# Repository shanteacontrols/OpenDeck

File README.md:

# OpenDeck

OpenDeck is a platform for building interactive control and sensing devices using MIDI and OSC. From USB MIDI DJ controllers and DAW control surfaces to Ethernet-connected OSC nodes, sensor interfaces and media installations, OpenDeck supports a wide range of hardware projects.

The main platform features:

* Browser-based configuration
* No firmware development required
* Hardware-independent - supports multiple MCU families and development boards
* MIDI and OSC support
* Extensible sensor support

The platform lets you focus on hardware and interaction design rather than tweaking and debugging firmware.

*Click the image below for a demo video of the [OpenDeck configurator](https://config.shanteacontrols.com)*

Configurator is available either [online](https://config.shanteacontrols.com) or [offline](https://github.com/shanteacontrols/OpenDeckUI/releases).

*Some of the devices built with OpenDeck*

## Peripherals

OpenDeck supports the following peripherals:

### Core I/O

* Buttons
* Encoders
* Single-color LEDs and other types of outputs such as relays or transistors
* Potentiometers
* FSRs (force-sensitive resistors)

### Displays

* [Nextion HMI](https://nextion.tech/) touchscreen displays
* [SSD1306 small OLED display](https://www.adafruit.com/product/326)

### Sensors

* [APDS-9960 proximity, light, RGB, and gesture sensor](https://www.adafruit.com/product/3595) - OSC only
* [CAP1188 8-Key Capacitive Touch Sensor](https://www.adafruit.com/product/1602) - OSC only
* [VL53L4CX time of flight distance sensor](https://www.adafruit.com/product/5425) - OSC only
* [VL53L5CX 8x8 time of flight distance sensor](https://www.sparkfun.com/sparkfun-qwiic-tof-imager-vl53l5cx.html) - OSC only
* [BNO085 9-DOF orientation IMU fusion sensor](https://www.adafruit.com/product/4754) - OSC only

Each sensor has specific configuration options such as smoothing, selectable event output etc.

## Features

OpenDeck provides extensive MIDI and OSC functionality:

* MIDI: sending of both 7-bit and 14-bit Non-Registered Parameter Numbers (NRPN), latching messages on buttons, various encoding modes for quadrature encoders, output control using MIDI In, configurable MIDI channels for each component individually, Bluetooth MIDI and more.
* OSC: Ethernet transport, configurable destinations, sensor data streaming, output control, automatic network discovery via mDNS, network-based configuration and firmware updates.

A detailed guide to all supported configurable features can be found [here](https://github.com/shanteacontrols/OpenDeck/wiki/Configurable-features).

If the feature you want isn't supported yet, don't feel discouraged. Open up a [discussion thread](https://github.com/shanteacontrols/OpenDeck/discussions) and let's talk about it.

## Official board

Currently, there is only one official board available to buy: the L variant, where "L" stands for "large". The board is available on [Lectronz store](https://lectronz.com/products/opendeck-l/).

This board is based on Raspberry Pi RP2040 microcontroller and features the following:

* 128 digital inputs
* 64 digital outputs
* 64 analog inputs
* DIN MIDI
* USB MIDI (USB C)
* Connector for touchscreen
* Connector for I2C OLED display
* Additional connectors with 3V+GND and 5V+GND connections

The L board doesn't have OSC support. It focuses on providing lots of I/O specifically for USB and DIN MIDI use-cases. OSC functionality is available on a number of supported Ethernet-enabled boards.

## Supported boards

The firmware supports various other boards, both small and large:

| Board | MIDI | OSC |
| --- | --- | --- |
| [Adafruit Grand Central M4 Express](https://www.adafruit.com/product/4064) | USB, DIN | No |
| [Adafruit Metro ESP32-S3](https://www.adafruit.com/product/5500) | USB, DIN | No |
| [Adafruit Metro ESP32-S3](https://www.adafruit.com/product/5500) + [W5500 Ethernet Shield](https://wiznet.io/products/open-source-hardware/w5500-ethernet-shield) | USB | Ethernet |
| [Adafruit Metro ESP32-S3](https://www.adafruit.com/product/5500) + [W6100 Ethernet Shield](https://wiznet.io/products/open-source-hardware/w6100-ethernet-shield) | USB | Ethernet |
| [Adafruit Metro RP2040](https://www.adafruit.com/product/5786) | USB, DIN | No |
| [Adafruit Metro RP2040](https://www.adafruit.com/product/5786) + [W5500 Ethernet Shield](https://wiznet.io/products/open-source-hardware/w5500-ethernet-shield) | USB | Ethernet |
| [Adafruit Metro RP2040](https://www.adafruit.com/product/5786) + [W6100 Ethernet Shield](https://wiznet.io/products/open-source-hardware/w6100-ethernet-shield) | USB | Ethernet |
| [Arduino Nano 33 BLE](https://store.arduino.cc/products/arduino-nano-33-ble) | USB, DIN, BLE | No |
| [LILYGO T-ETH Elite](https://lilygo.cc/products/t-eth-elite-1) | USB | Ethernet |
| [nRF52840 DK](https://www.nordicsemi.com/Products/Development-hardware/nrf52840-dk) | USB, DIN, BLE | No |
| [nRF5340 DK](https://www.nordicsemi.com/Products/Development-hardware/nrf5340-dk) | USB, DIN, BLE | No |
| [Olimex ESP32-POE](https://www.olimex.com/Products/IoT/ESP32/ESP32-POE/open-source-hardware) | No | Ethernet |
| [Raspberry Pi Pico](https://www.raspberrypi.com/products/raspberry-pi-pico/) | USB, DIN | No |
| [Raspberry Pi Pico 2](https://www.raspberrypi.com/products/raspberry-pi-pico-2/) | USB, DIN | No |
| [ST Discovery F407VG](https://www.st.com/en/evaluation-tools/stm32f4discovery.html) | USB, DIN | No |
| [ST Nucleo F767ZI](https://www.st.com/en/evaluation-tools/nucleo-f767zi.html) | DIN | Ethernet |
| [ST Nucleo H563ZI](https://www.st.com/en/evaluation-tools/nucleo-h563zi.html) | DIN | Ethernet |
| [ST Nucleo H753ZI](https://www.st.com/en/evaluation-tools/nucleo-h753zi.html) | DIN | Ethernet |
| [STM32F411 Black Pill V3+](https://www.adafruit.com/product/4877) with populated external flash | USB, DIN | No |
| [Teensy 4.0](https://www.pjrc.com/store/teensy40.html) | USB, DIN | No |
| [Teensy 4.1](https://www.pjrc.com/store/teensy41.html) | USB, DIN | No |
| [Waveshare Core405R](https://www.waveshare.com/core405r.htm) | USB, DIN | No |
| [Waveshare ESP32-S3-ETH](https://www.waveshare.com/esp32-s3-eth.htm) | USB | Ethernet |
| [W5500-EVB-Pico](https://docs.wiznet.io/Product/Open-Source-Hardware/w5500-evb-pico) | USB | Ethernet |
| [W5500-EVB-Pico2](https://docs.wiznet.io/Product/Open-Source-Hardware/w5500-evb-pico2) | USB, DIN | Ethernet |
| [W6100-EVB-Pico](https://docs.wiznet.io/Product/Open-Source-Hardware/w6100-evb-pico) | USB, DIN | Ethernet |
| [W6100-EVB-Pico2](https://docs.wiznet.io/Product/Open-Source-Hardware/w6100-evb-pico2) | USB, DIN | Ethernet |
| [wESP32](https://wesp32.com/) | No | Ethernet |

For more details on supported boards, check the [wiki page](https://github.com/shanteacontrols/OpenDeck/wiki). Support for custom boards [can also be added](https://github.com/shanteacontrols/OpenDeck/wiki/Creating-custom-board-variant).

## Documentation

Available on dedicated [Wiki section](https://github.com/shanteacontrols/OpenDeck/wiki/).

## Discussion

Need help? Want to show off your OpenDeck-based builds? Head over to [Discussions](https://github.com/shanteacontrols/OpenDeck/discussions)!

## License

OpenDeck source code is available under Apache License v2.0. Zephyr RTOS, which OpenDeck is built on top of, is also licensed under Apache License v2.0.

Third-party components with different licenses:

* `u8g2`: Two-clause BSD
* `vl53l4cx`: Three-clause BSD
* `vl53l5cx`: Three-clause BSD
* `zlibs`: MIT

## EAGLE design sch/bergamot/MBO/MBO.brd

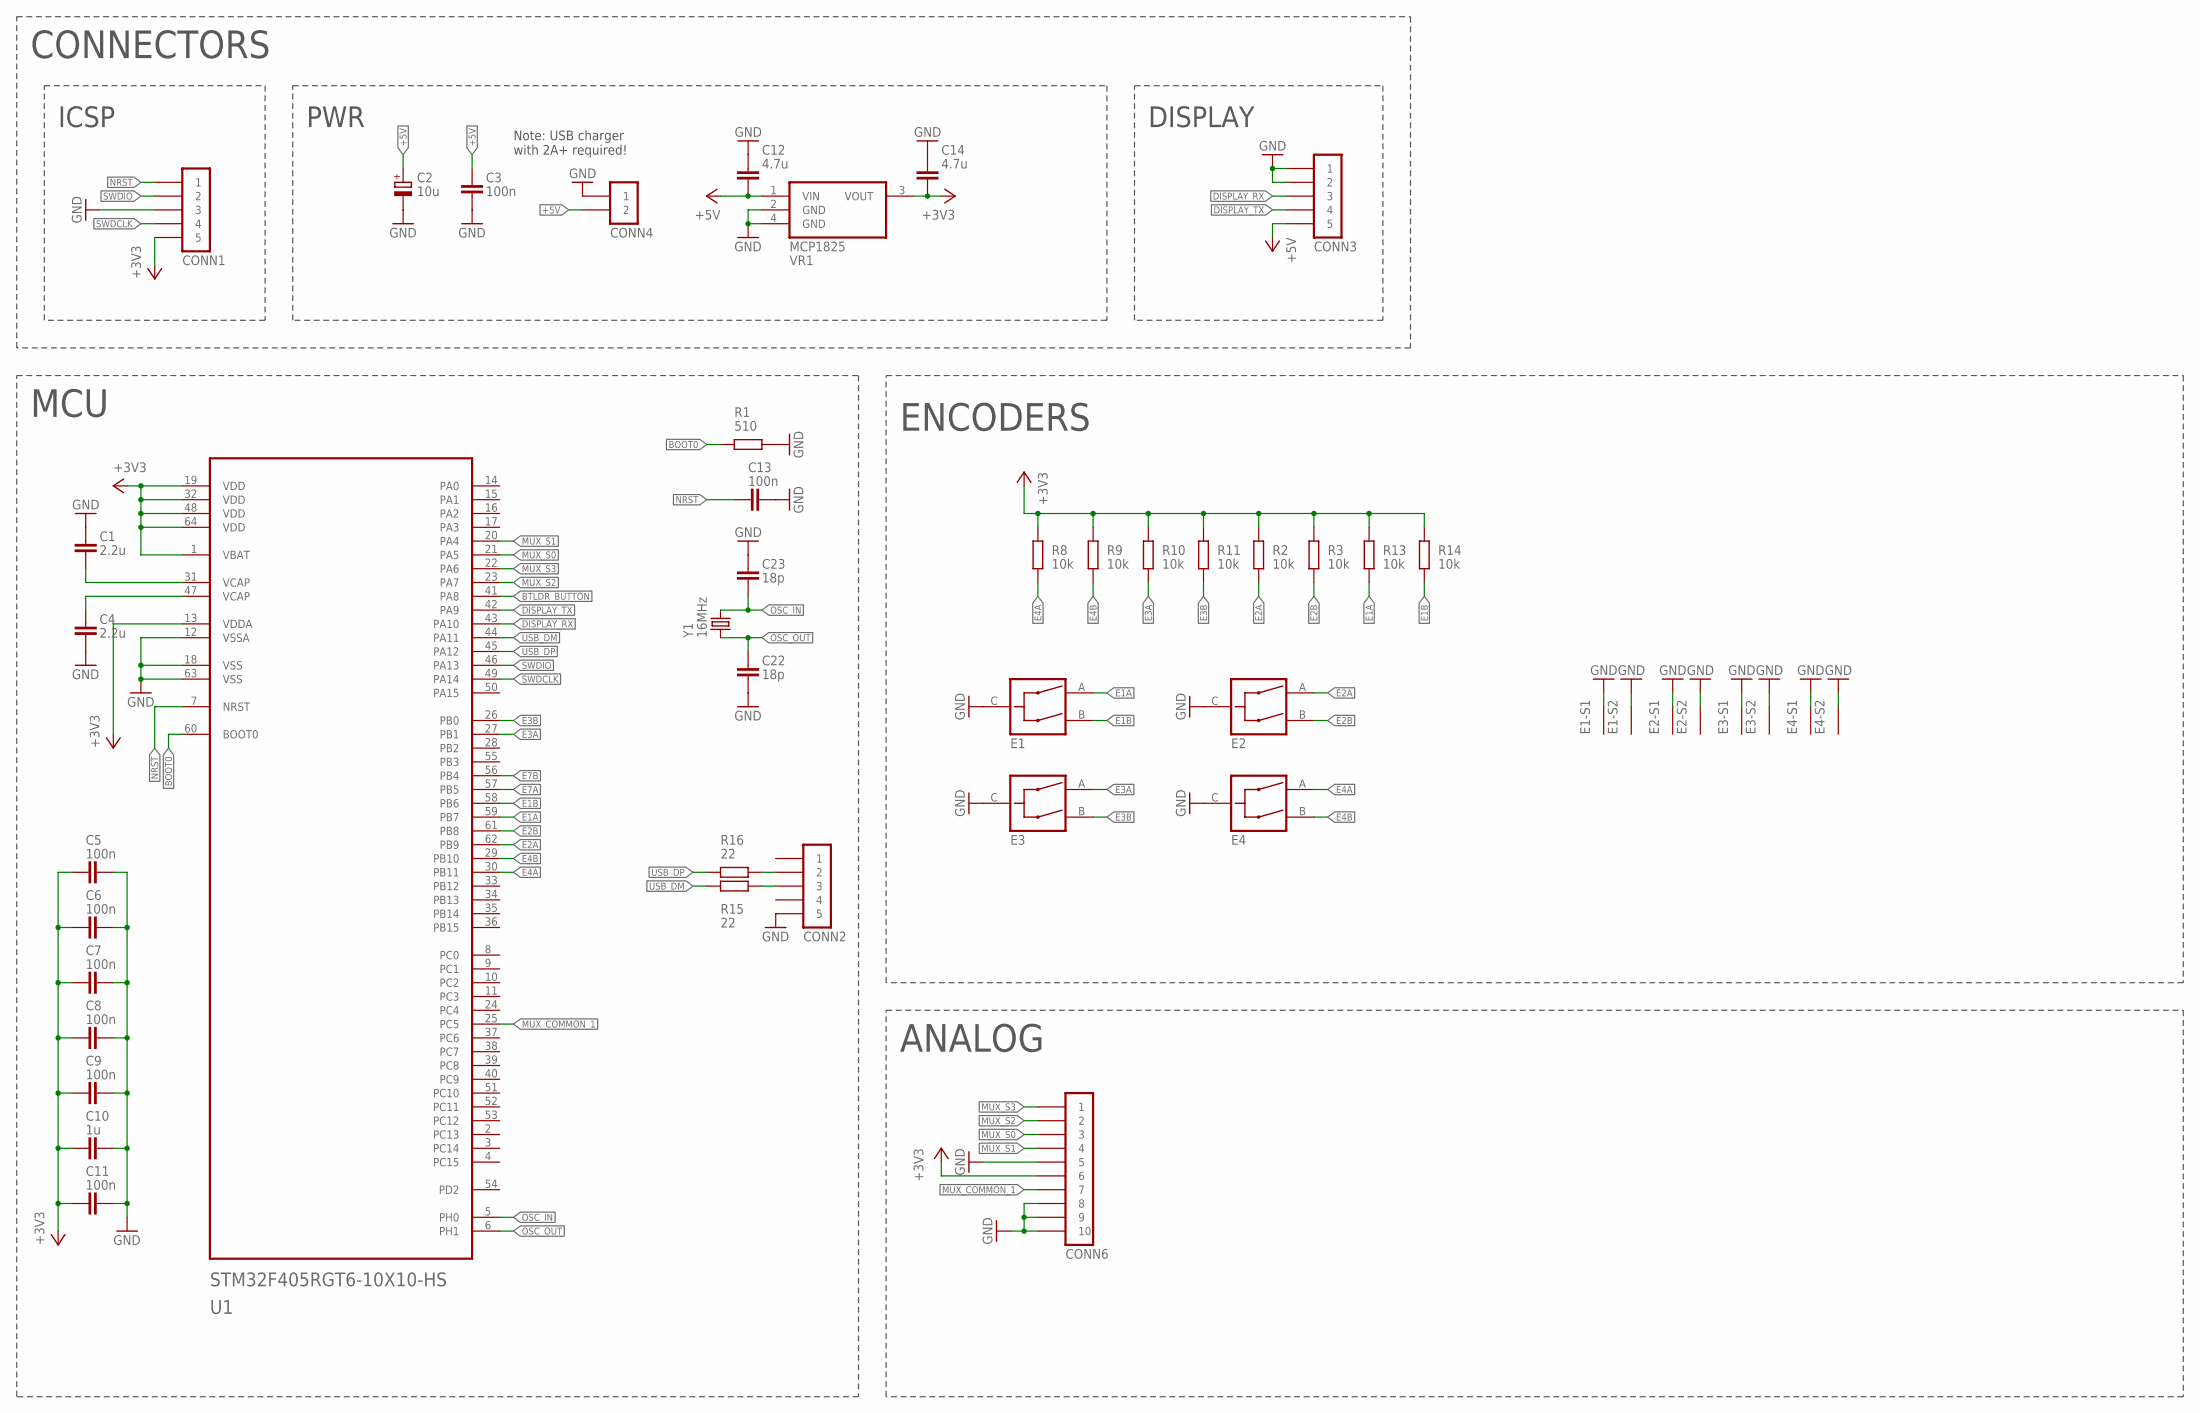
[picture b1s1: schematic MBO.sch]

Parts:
C1, C4: 2.2u; C0805
C2: 10u; C-TH-E-0401
C3, C5, C6, C7, C8, C9, C11, C13: 100n; C0805
C10: 1u; C0805
C12, C14: 4.7u; C0805
C22, C23: 18p; C0805
CONN1: PINHD-1X05-TH-2.54MM; 1X05-2.54
CONN2, CONN3: PINHD-1X05-JST-XH-H; JST-XH-05P-H
CONN4: PINHD-1X02-JST-XH-H; JST-XH-02P-H
CONN6: PINHD-1X10-FFC-1MM-Z; MOLEX-52271-1079
E1, E2, E3, E4: ALPS-EC12E24404AX; EC12E-1
R1: 510; R0805
R2, R3, R8, R9, R10, R11, R13, R14: 10k; R0805
R15, R16: 22; R0805
U1: STM32F405RGT6-10X10-HS; TQFP-64-10X10-HS
VR1: MCP1825; SOT223
Y1: 16MHz; HC49US

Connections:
+3V3: C5.1, C6.1, C7.1, C8.1, C9.1, C10.1, C11.1, C14.1, CONN1.5, CONN6.6, R2.2, R3.2, R8.2, R9.2, R10.2, R11.2, R13.2, R14.2, U1.1 (VBAT), U1.13 (VDDA), U1.19 (VDD), U1.32 (VDD), U1.48 (VDD), U1.64 (VDD), VR1.3 (VOUT)
+5V: C2.+, C3.1, C12.1, CONN3.5, CONN4.2, VR1.1 (VIN)
BOOT0: R1.1, U1.60 (BOOT0)
BTLDR_BUTTON: U1.41 (PA8)
DISPLAY_RX: CONN3.3, U1.43 (PA10)
DISPLAY_TX: CONN3.4, U1.42 (PA9)
E1A: E1.A, R13.1, U1.59 (PB7)
E1B: E1.B, R14.1, U1.58 (PB6)
E2A: E2.A, R2.1, U1.62 (PB9)
E2B: E2.B, R3.1, U1.61 (PB8)
E3A: E3.A, R10.1, U1.27 (PB1)
E3B: E3.B, R11.1, U1.26 (PB0)
E4A: E4.A, R8.1, U1.30 (PB11)
E4B: E4.B, R9.1, U1.29 (PB10)
E7A: U1.57 (PB5)
E7B: U1.56 (PB4)
GND: C1.1, C2.-, C3.2, C4.2, C5.2, C6.2, C7.2, C8.2, C9.2, C10.2, C11.2, C12.2, C13.2, C14.2, C22.2, C23.1, CONN1.3, CONN2.5, CONN3.1, CONN3.2, CONN4.1, CONN6.5, CONN6.8, CONN6.9, CONN6.10, E1.C, E1.S1 (S), E1.S2 (S), E2.C, E2.S1 (S), E2.S2 (S), E3.C, E3.S1 (S), E3.S2 (S), E4.C, E4.S1 (S), E4.S2 (S), R1.2, U1.12 (VSSA), U1.18 (VSS), U1.63 (VSS), VR1.2 (GND), VR1.4 (GND)
MUX_COMMON_1: CONN6.7, U1.25 (PC5)
MUX_S0: CONN6.3, U1.21 (PA5)
MUX_S1: CONN6.4, U1.20 (PA4)
MUX_S2: CONN6.2, U1.23 (PA7)
MUX_S3: CONN6.1, U1.22 (PA6)
unnamed: C1.2, U1.31 (VCAP)
unnamed: C4.1, U1.47 (VCAP)
NRST: C13.1, CONN1.1, U1.7 (NRST)
OSC_IN: C23.2, U1.5 (PH0), Y1.2
OSC_OUT: C22.1, U1.6 (PH1), Y1.1
SWDCLK: CONN1.4, U1.49 (PA14)
SWDIO: CONN1.2, U1.46 (PA13)
USB_DM: R15.1, U1.44 (PA11)
USB_DM_ESD: CONN2.3, R15.2
USB_DP: R16.1, U1.45 (PA12)
USB_DP_ESD: CONN2.2, R16.2

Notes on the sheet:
MCU
CONNECTORS
ICSP
PWR
ENCODERS
DISPLAY
Note: USB charger with 2A+ required!
ANALOG

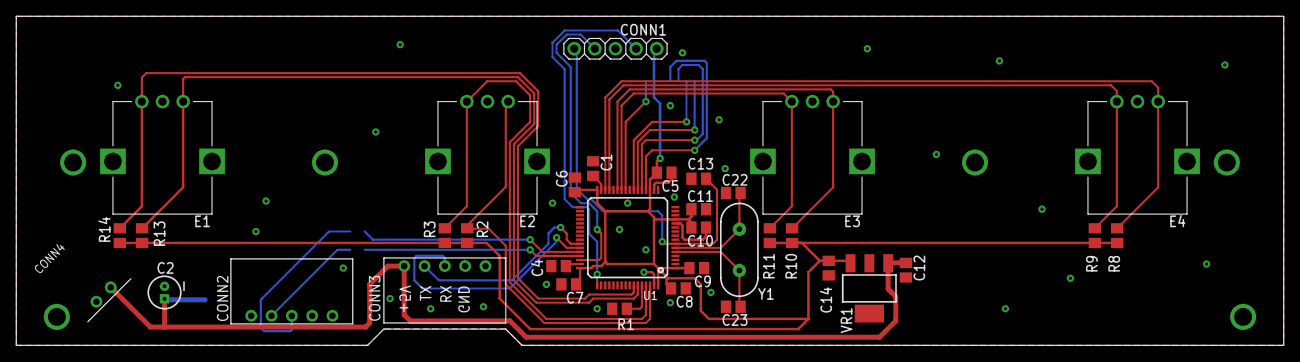
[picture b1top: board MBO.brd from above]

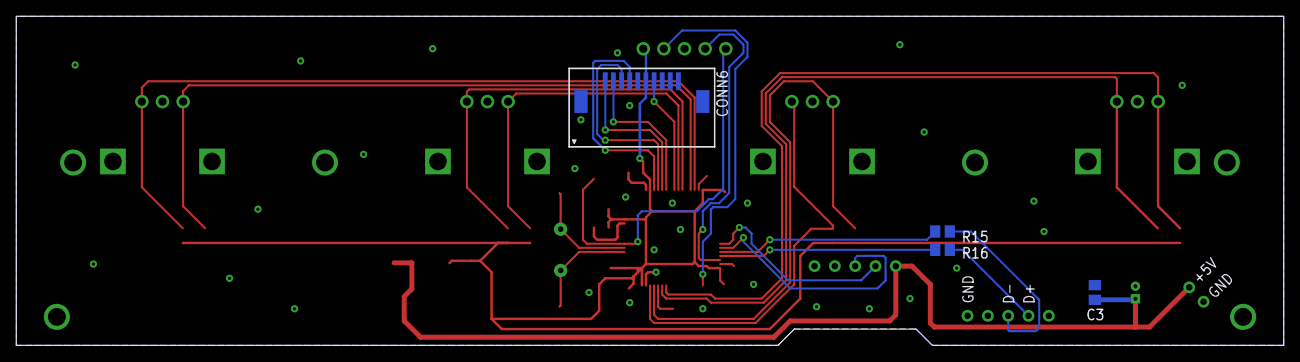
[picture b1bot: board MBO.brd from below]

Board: 2 copper layers, 156.0 x 40.5 mm, 39 parts (4 on the bottom side), 30 nets.

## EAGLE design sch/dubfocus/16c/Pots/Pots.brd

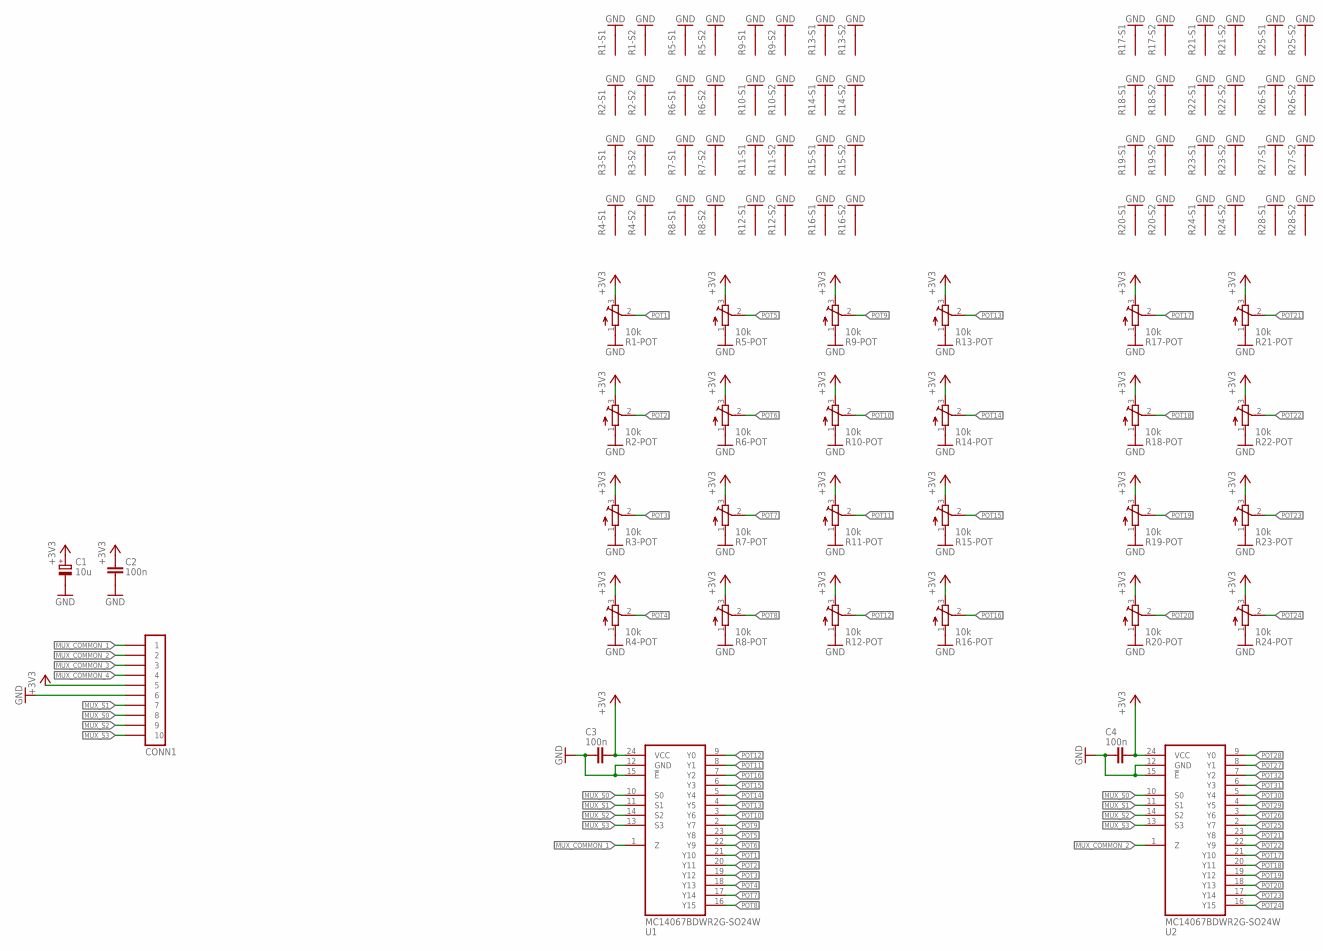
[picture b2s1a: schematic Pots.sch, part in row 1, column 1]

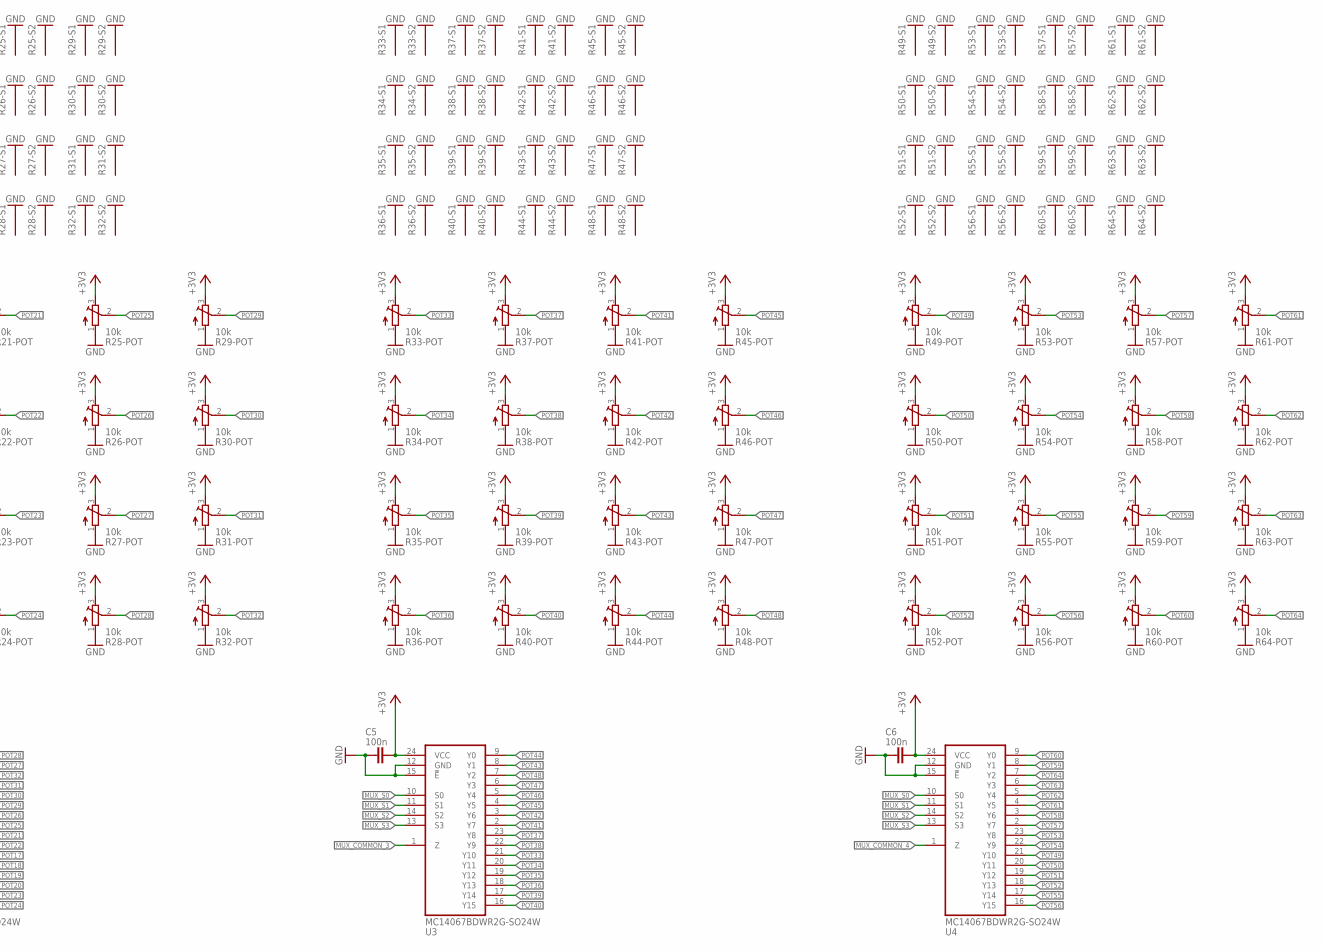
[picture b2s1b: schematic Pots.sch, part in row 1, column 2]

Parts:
C1: 10u; C-TH-E-0401
C2, C3, C4, C5, C6: 100n; C0805
CONN1: PINHD-1X10-FFC-1MM-Z; MOLEX-52271-1079
R1, R2, R3, R4, R5, R6, R7, R8, R9, R10, R11, R12, R13, R14, R15, R16, R17, R18, R19, R20, R21, R22, R23, R24, R25, R26, R27, R28, R29, R30, R31, R32, R33, R34, R35, R36, R37, R38, R39, R40, R41, R42, R43, R44, R45, R46, R47, R48, R49, R50, R51, R52, R53, R54, R55, R56, R57, R58, R59, R60, R61, R62, R63, R64: 10k; PTV09A-4025F-B103
U1, U2, U3, U4: MC14067BDWR2G-SO24W; SO24-W

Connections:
+3V3: C1.+, C2.1, C3.2, C4.2, C5.2, C6.2, CONN1.5, R1.3, R2.3, R3.3, R4.3, R5.3, R6.3, R7.3, R8.3, R9.3, R10.3, R11.3, R12.3, R13.3, R14.3, R15.3, R16.3, R17.3, R18.3, R19.3, R20.3, R21.3, R22.3, R23.3, R24.3, R25.3, R26.3, R27.3, R28.3, R29.3, R30.3, R31.3, R32.3, R33.3, R34.3, R35.3, R36.3, R37.3, R38.3, R39.3, R40.3, R41.3, R42.3, R43.3, R44.3, R45.3, R46.3, R47.3, R48.3, R49.3, R50.3, R51.3, R52.3, R53.3, R54.3, R55.3, R56.3, R57.3, R58.3, R59.3, R60.3, R61.3, R62.3, R63.3, R64.3, U1.24 (VCC), U2.24 (VCC), U3.24 (VCC), U4.24 (VCC)
GND: C1.-, C2.2, C3.1, C4.1, C5.1, C6.1, CONN1.6, R1.1, R1.S1 (S), R1.S2 (S), R2.1, R2.S1 (S), R2.S2 (S), R3.1, R3.S1 (S), R3.S2 (S), R4.1, R4.S1 (S), R4.S2 (S), R5.1, R5.S1 (S), R5.S2 (S), R6.1, R6.S1 (S), R6.S2 (S), R7.1, R7.S1 (S), R7.S2 (S), R8.1, R8.S1 (S), R8.S2 (S), R9.1, R9.S1 (S), R9.S2 (S), R10.1, R10.S1 (S), R10.S2 (S), R11.1, R11.S1 (S), R11.S2 (S), R12.1, R12.S1 (S), R12.S2 (S), R13.1, R13.S1 (S), R13.S2 (S), R14.1, R14.S1 (S), R14.S2 (S), R15.1, R15.S1 (S), R15.S2 (S), R16.1, R16.S1 (S), R16.S2 (S), R17.1, R17.S1 (S), R17.S2 (S), R18.1, R18.S1 (S), R18.S2 (S), R19.1, R19.S1 (S), R19.S2 (S), R20.1, R20.S1 (S), R20.S2 (S), R21.1, R21.S1 (S), R21.S2 (S), R22.1, R22.S1 (S), R22.S2 (S), R23.1, R23.S1 (S), R23.S2 (S), R24.1, R24.S1 (S), R24.S2 (S), R25.1, R25.S1 (S), R25.S2 (S), R26.1, R26.S1 (S), R26.S2 (S), R27.1, R27.S1 (S), R27.S2 (S), R28.1, R28.S1 (S), R28.S2 (S), R29.1, R29.S1 (S), R29.S2 (S), R30.1, R30.S1 (S), R30.S2 (S), R31.1, R31.S1 (S), R31.S2 (S), R32.1, R32.S1 (S), R32.S2 (S), R33.1, R33.S1 (S), R33.S2 (S), R34.1, R34.S1 (S), R34.S2 (S), R35.1, R35.S1 (S), R35.S2 (S), R36.1, R36.S1 (S), R36.S2 (S), R37.1, R37.S1 (S), R37.S2 (S), R38.1, R38.S1 (S), R38.S2 (S), R39.1, R39.S1 (S), R39.S2 (S), R40.1, R40.S1 (S), R40.S2 (S), R41.1, R41.S1 (S), R41.S2 (S), R42.1, R42.S1 (S), R42.S2 (S), R43.1, R43.S1 (S), R43.S2 (S), R44.1, R44.S1 (S), R44.S2 (S), R45.1, R45.S1 (S), R45.S2 (S), R46.1, R46.S1 (S), R46.S2 (S), R47.1, R47.S1 (S), R47.S2 (S), R48.1, R48.S1 (S), R48.S2 (S), R49.1, R49.S1 (S), R49.S2 (S), R50.1, R50.S1 (S), R50.S2 (S), R51.1, R51.S1 (S), R51.S2 (S), R52.1, R52.S1 (S), R52.S2 (S), R53.1, R53.S1 (S), R53.S2 (S), R54.1, R54.S1 (S), R54.S2 (S), R55.1, R55.S1 (S), R55.S2 (S), R56.1, R56.S1 (S), R56.S2 (S), R57.1, R57.S1 (S), R57.S2 (S), R58.1, R58.S1 (S), R58.S2 (S), R59.1, R59.S1 (S), R59.S2 (S), R60.1, R60.S1 (S), R60.S2 (S), R61.1, R61.S1 (S), R61.S2 (S), R62.1, R62.S1 (S), R62.S2 (S), R63.1, R63.S1 (S), R63.S2 (S), R64.1, R64.S1 (S), R64.S2 (S), U1.12 (GND), U1.15 (!E), U2.12 (GND), U2.15 (!E), U3.12 (GND), U3.15 (!E), U4.12 (GND), U4.15 (!E)
MUX_COMMON_1: CONN1.1, U1.1 (Z)
MUX_COMMON_2: CONN1.2, U2.1 (Z)
MUX_COMMON_3: CONN1.3, U3.1 (Z)
MUX_COMMON_4: CONN1.4, U4.1 (Z)
MUX_S0: CONN1.8, U1.10 (S0), U2.10 (S0), U3.10 (S0), U4.10 (S0)
MUX_S1: CONN1.7, U1.11 (S1), U2.11 (S1), U3.11 (S1), U4.11 (S1)
MUX_S2: CONN1.9, U1.14 (S2), U2.14 (S2), U3.14 (S2), U4.14 (S2)
MUX_S3: CONN1.10, U1.13 (S3), U2.13 (S3), U3.13 (S3), U4.13 (S3)
POT1: R1.2, U1.21 (Y10)
POT2: R2.2, U1.20 (Y11)
POT3: R3.2, U1.19 (Y12)
POT4: R4.2, U1.18 (Y13)
POT5: R5.2, U1.23 (Y8)
POT6: R6.2, U1.22 (Y9)
POT7: R7.2, U1.17 (Y14)
POT8: R8.2, U1.16 (Y15)
POT9: R9.2, U1.2 (Y7)
POT10: R10.2, U1.3 (Y6)
POT11: R11.2, U1.8 (Y1)
POT12: R12.2, U1.9 (Y0)
POT13: R13.2, U1.4 (Y5)
POT14: R14.2, U1.5 (Y4)
POT15: R15.2, U1.6 (Y3)
POT16: R16.2, U1.7 (Y2)
POT17: R17.2, U2.21 (Y10)
POT18: R18.2, U2.20 (Y11)
POT19: R19.2, U2.19 (Y12)
POT20: R20.2, U2.18 (Y13)
POT21: R21.2, U2.23 (Y8)
POT22: R22.2, U2.22 (Y9)
POT23: R23.2, U2.17 (Y14)
POT24: R24.2, U2.16 (Y15)
POT25: R25.2, U2.2 (Y7)
POT26: R26.2, U2.3 (Y6)
POT27: R27.2, U2.8 (Y1)
POT28: R28.2, U2.9 (Y0)
POT29: R29.2, U2.4 (Y5)
POT30: R30.2, U2.5 (Y4)
POT31: R31.2, U2.6 (Y3)
POT32: R32.2, U2.7 (Y2)
POT33: R33.2, U3.21 (Y10)
POT34: R34.2, U3.20 (Y11)
POT35: R35.2, U3.19 (Y12)
POT36: R36.2, U3.18 (Y13)
POT37: R37.2, U3.23 (Y8)
POT38: R38.2, U3.22 (Y9)
POT39: R39.2, U3.17 (Y14)
POT40: R40.2, U3.16 (Y15)
POT41: R41.2, U3.2 (Y7)
POT42: R42.2, U3.3 (Y6)
POT43: R43.2, U3.8 (Y1)
POT44: R44.2, U3.9 (Y0)
POT45: R45.2, U3.4 (Y5)
POT46: R46.2, U3.5 (Y4)
POT47: R47.2, U3.6 (Y3)
POT48: R48.2, U3.7 (Y2)
POT49: R49.2, U4.21 (Y10)
POT50: R50.2, U4.20 (Y11)
POT51: R51.2, U4.19 (Y12)
POT52: R52.2, U4.18 (Y13)
POT53: R53.2, U4.23 (Y8)
POT54: R54.2, U4.22 (Y9)
POT55: R55.2, U4.17 (Y14)
POT56: R56.2, U4.16 (Y15)
POT57: R57.2, U4.2 (Y7)
POT58: R58.2, U4.3 (Y6)
POT59: R59.2, U4.8 (Y1)
POT60: R60.2, U4.9 (Y0)
POT61: R61.2, U4.4 (Y5)
POT62: R62.2, U4.5 (Y4)
POT63: R63.2, U4.6 (Y3)
POT64: R64.2, U4.7 (Y2)

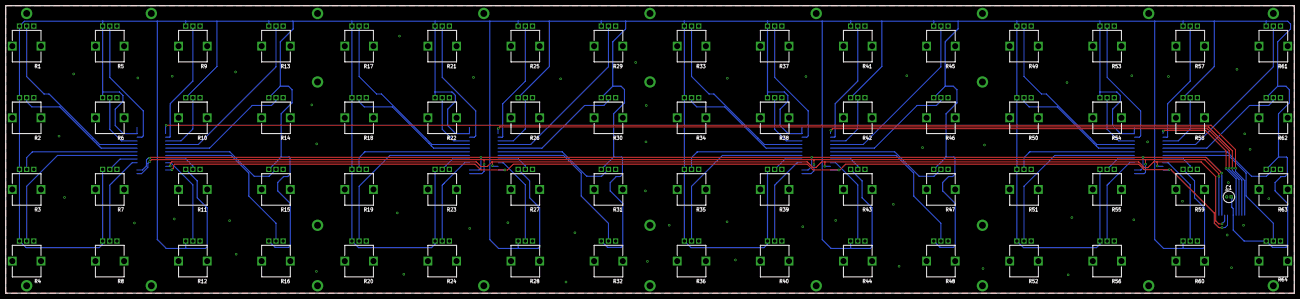
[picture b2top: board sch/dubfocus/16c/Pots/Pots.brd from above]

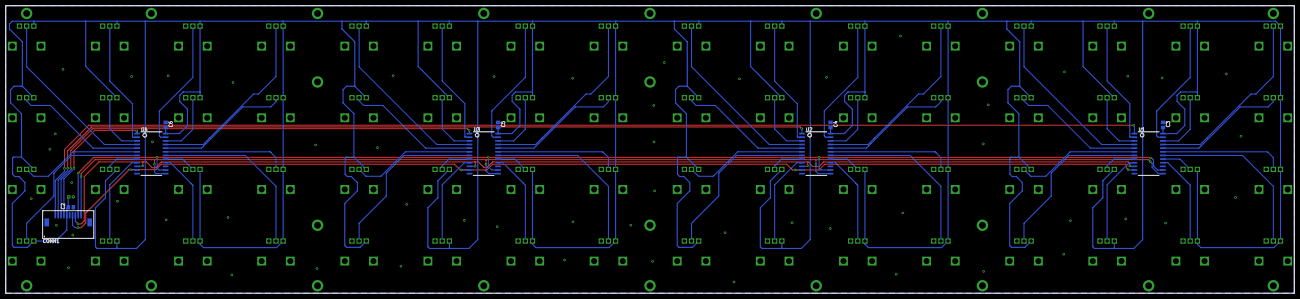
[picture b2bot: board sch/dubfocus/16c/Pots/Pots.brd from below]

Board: 2 copper layers, 449.6 x 100.3 mm, 75 parts (10 on the bottom side), 74 nets.

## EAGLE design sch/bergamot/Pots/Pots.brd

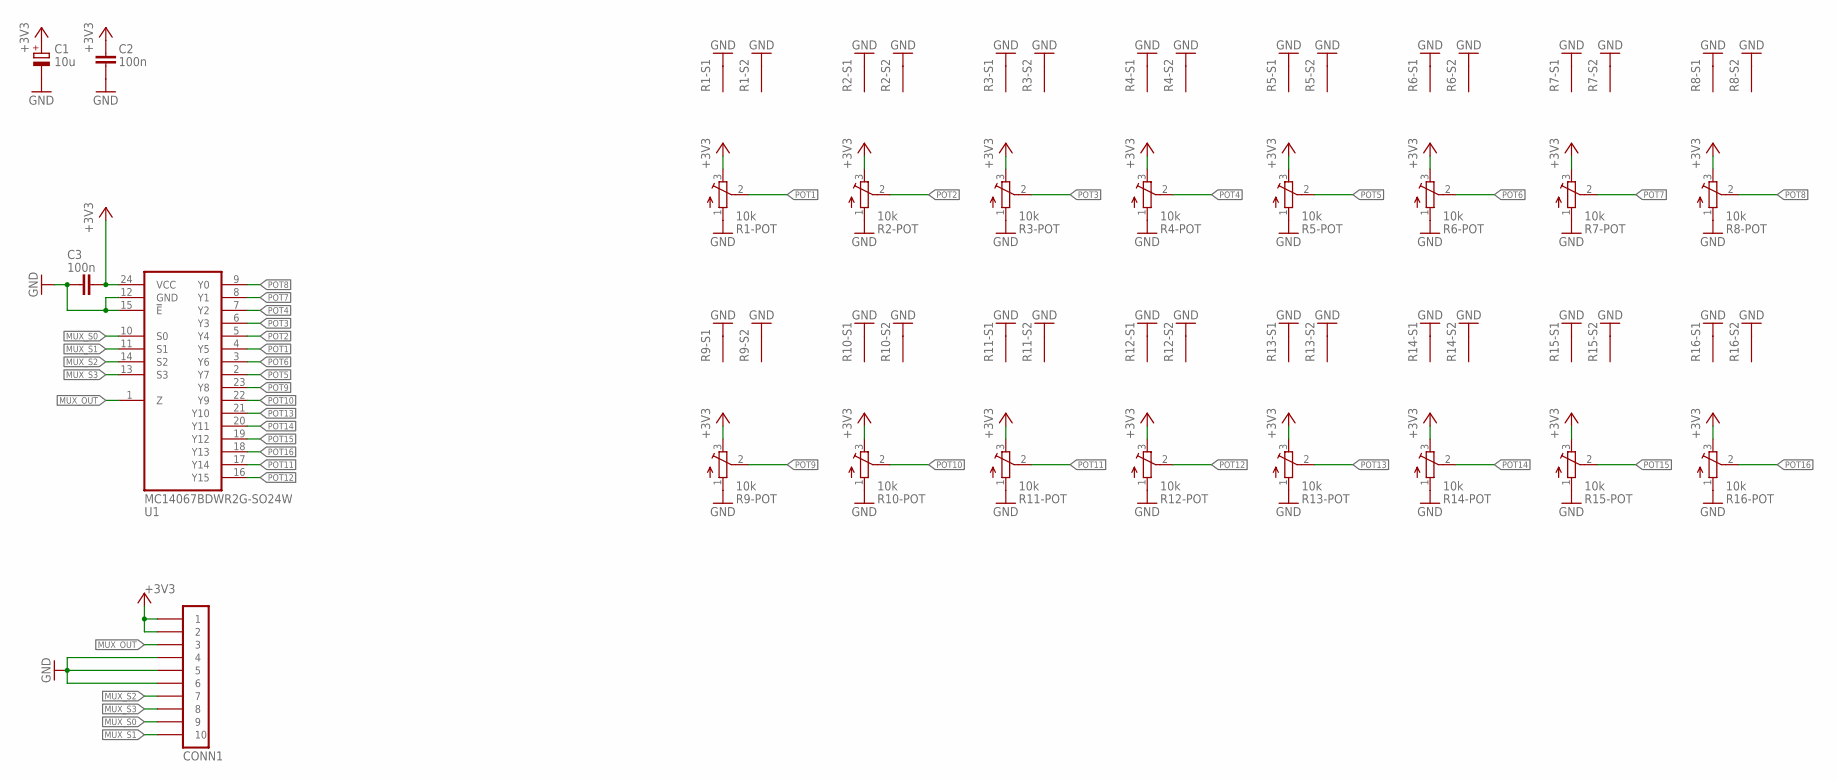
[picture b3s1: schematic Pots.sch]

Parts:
C1: 10u; 153CLV-0405
C2, C3: 100n; C0805
CONN1: PINHD-1X10-FFC-1MM-Z; MOLEX-52271-1079
R1, R2, R3, R4, R5, R6, R7, R8, R9, R10, R11, R12, R13, R14, R15, R16: 10k; PTV09A-4025F-B103
U1: MC14067BDWR2G-SO24W; SO24-W

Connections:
+3V3: C1.+, C2.1, C3.2, CONN1.1, CONN1.2, R1.3, R2.3, R3.3, R4.3, R5.3, R6.3, R7.3, R8.3, R9.3, R10.3, R11.3, R12.3, R13.3, R14.3, R15.3, R16.3, U1.24 (VCC)
GND: C1.-, C2.2, C3.1, CONN1.4, CONN1.5, CONN1.6, R1.1, R1.S1 (S), R1.S2 (S), R2.1, R2.S1 (S), R2.S2 (S), R3.1, R3.S1 (S), R3.S2 (S), R4.1, R4.S1 (S), R4.S2 (S), R5.1, R5.S1 (S), R5.S2 (S), R6.1, R6.S1 (S), R6.S2 (S), R7.1, R7.S1 (S), R7.S2 (S), R8.1, R8.S1 (S), R8.S2 (S), R9.1, R9.S1 (S), R9.S2 (S), R10.1, R10.S1 (S), R10.S2 (S), R11.1, R11.S1 (S), R11.S2 (S), R12.1, R12.S1 (S), R12.S2 (S), R13.1, R13.S1 (S), R13.S2 (S), R14.1, R14.S1 (S), R14.S2 (S), R15.1, R15.S1 (S), R15.S2 (S), R16.1, R16.S1 (S), R16.S2 (S), U1.12 (GND), U1.15 (!E)
MUX_OUT: CONN1.3, U1.1 (Z)
MUX_S0: CONN1.9, U1.10 (S0)
MUX_S1: CONN1.10, U1.11 (S1)
MUX_S2: CONN1.7, U1.14 (S2)
MUX_S3: CONN1.8, U1.13 (S3)
POT1: R1.2, U1.4 (Y5)
POT2: R2.2, U1.5 (Y4)
POT3: R3.2, U1.6 (Y3)
POT4: R4.2, U1.7 (Y2)
POT5: R5.2, U1.2 (Y7)
POT6: R6.2, U1.3 (Y6)
POT7: R7.2, U1.8 (Y1)
POT8: R8.2, U1.9 (Y0)
POT9: R9.2, U1.23 (Y8)
POT10: R10.2, U1.22 (Y9)
POT11: R11.2, U1.17 (Y14)
POT12: R12.2, U1.16 (Y15)
POT13: R13.2, U1.21 (Y10)
POT14: R14.2, U1.20 (Y11)
POT15: R15.2, U1.19 (Y12)
POT16: R16.2, U1.18 (Y13)

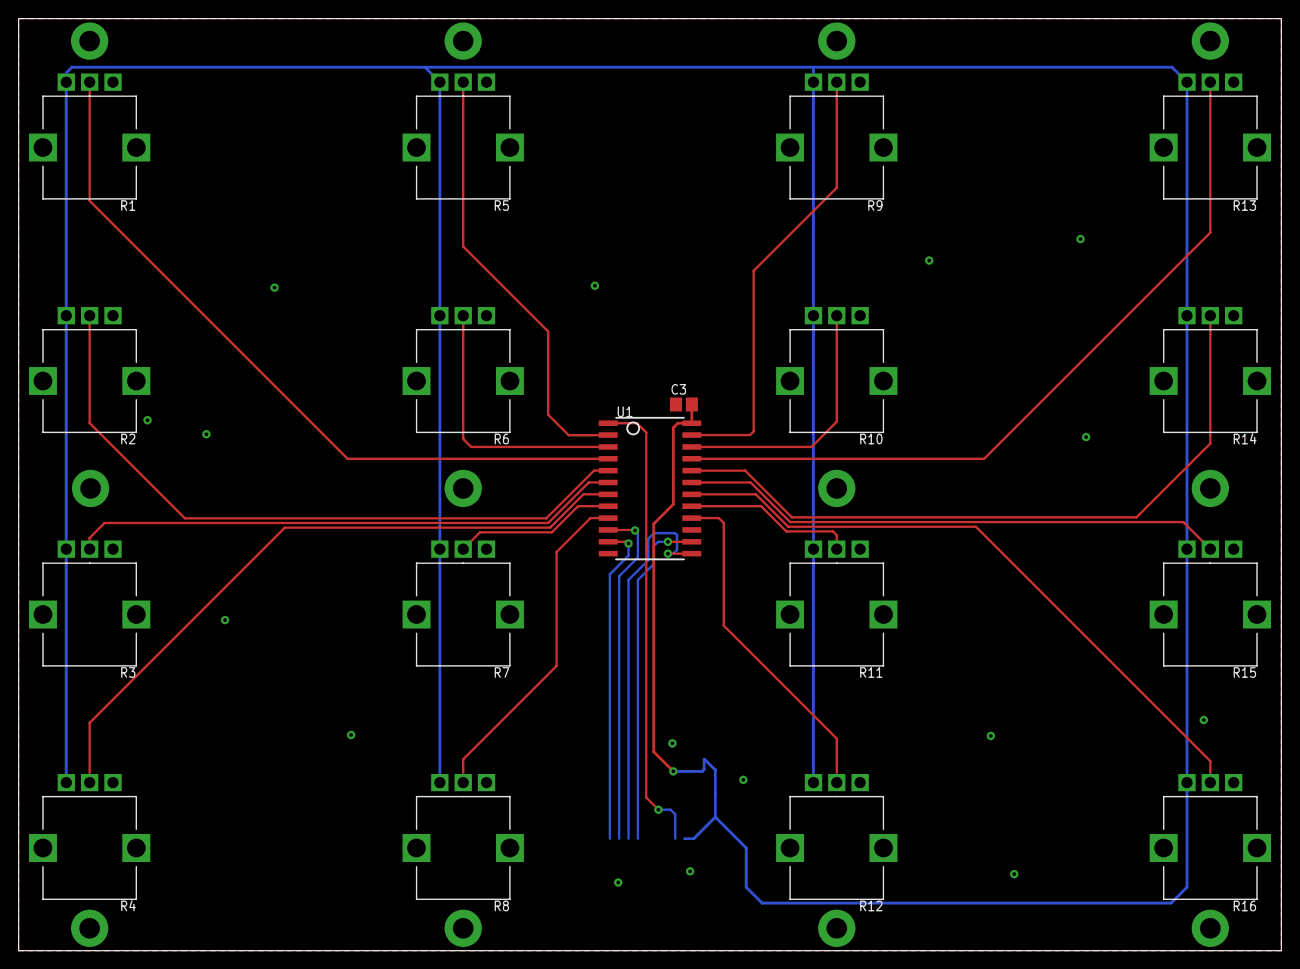
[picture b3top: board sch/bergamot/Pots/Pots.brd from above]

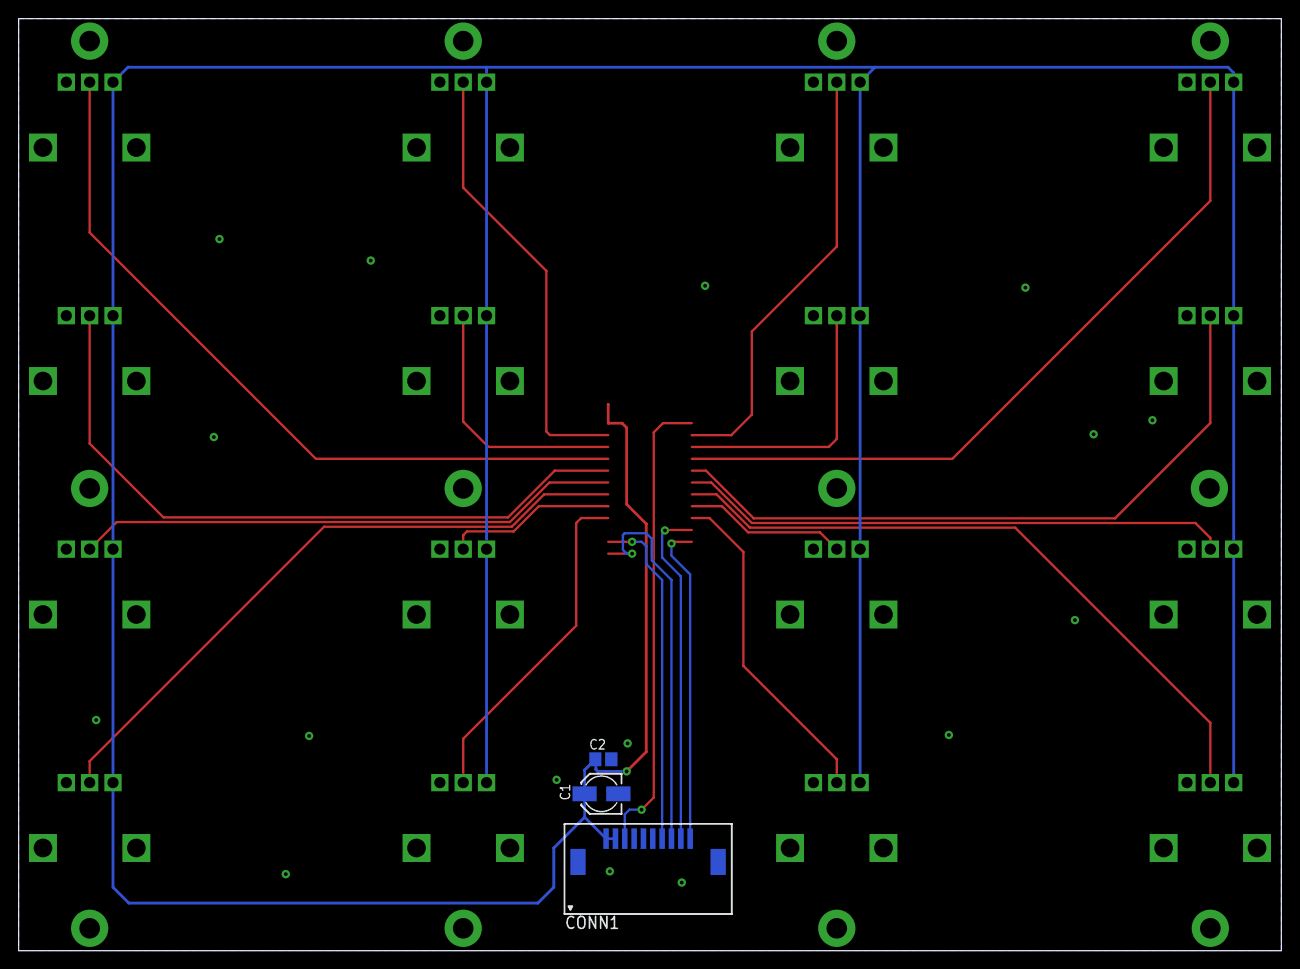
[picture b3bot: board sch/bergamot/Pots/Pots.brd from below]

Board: 2 copper layers, 135.2 x 99.8 mm, 21 parts (3 on the bottom side), 23 nets.
